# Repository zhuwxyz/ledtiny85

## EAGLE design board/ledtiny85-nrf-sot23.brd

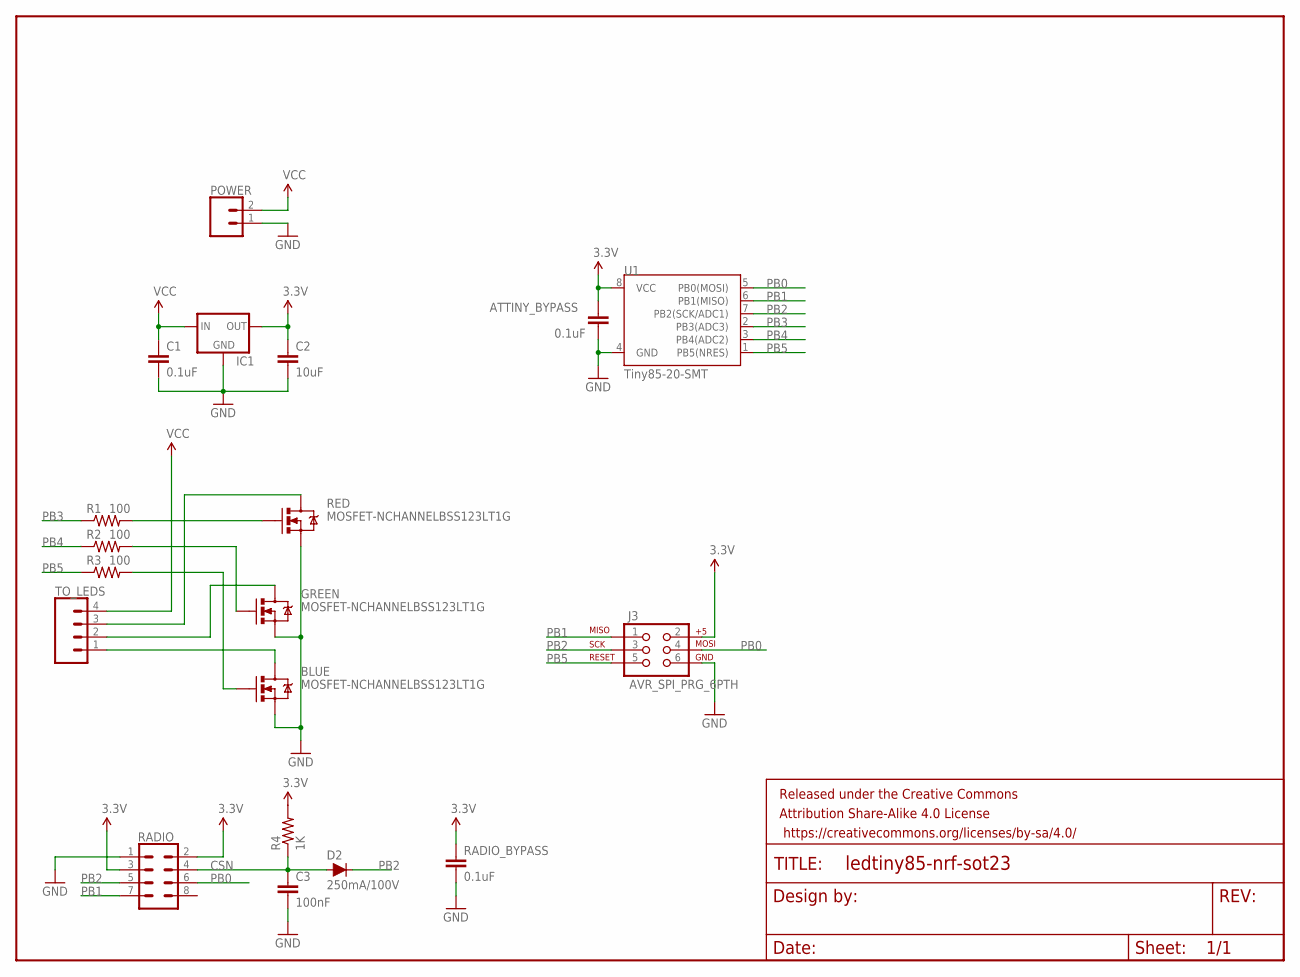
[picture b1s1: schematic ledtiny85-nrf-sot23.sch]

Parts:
ATTINY_BYPASS: 0.1uF; 0805
BLUE: MOSFET-NCHANNELBSS123LT1G; SOT23-3
C1: 0.1uF; 0805
C2: 10uF; 0805
C3: 100nF; 0805
D2: 250mA/100V; SOD-323
FRAME1: FRAME-LETTER; CREATIVE_COMMONS
GREEN: MOSFET-NCHANNELBSS123LT1G; SOT23-3
IC1: XC63FPM; SOT23
J3: AVR_SPI_PRG_6PTH; 2X3
POWER: CONN_02; 1X02
R1, R2, R3: 100; 0805
R4: 1K; 0805
RADIO: CONN_04X2; 2X4
RADIO_BYPASS: 0.1uF; 0805
RED: MOSFET-NCHANNELBSS123LT1G; SOT23-3
TO_LEDS: CONN_04; 1X04
U1: Tiny85-20-SMT; SO08-EIAJ

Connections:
3.3V: ATTINY_BYPASS.1, C2.1, IC1.2 (OUT), J3.2, R4.2, RADIO.2, RADIO.3, RADIO_BYPASS.1, U1.8 (VCC)
BLUE: BLUE.3 (D), TO_LEDS.1
CSN: C3.1, D2.A, R4.1, RADIO.4
GND: ATTINY_BYPASS.2, BLUE.2 (S), C1.2, C2.2, C3.2, GREEN.2 (S), IC1.1 (GND), J3.6, POWER.1, RADIO.1, RADIO_BYPASS.2, RED.2 (S), U1.4 (GND)
GREEN: GREEN.3 (D), TO_LEDS.2
unnamed: R1.2, RED.1 (G)
unnamed: GREEN.1 (G), R2.2
unnamed: BLUE.1 (G), R3.2
PB0: J3.4, RADIO.6, U1.5 (PB0(MOSI))
PB1: J3.1, RADIO.7, U1.6 (PB1(MISO))
PB2: D2.C, J3.3, RADIO.5, U1.7 (PB2(SCK/ADC1))
PB3: R1.1, U1.2 (PB3(ADC3))
PB4: R2.1, U1.3 (PB4(ADC2))
PB5: J3.5, R3.1, U1.1 (PB5(NRES))
RED: RED.3 (D), TO_LEDS.3
VCC: C1.1, IC1.3 (IN), POWER.2, TO_LEDS.4

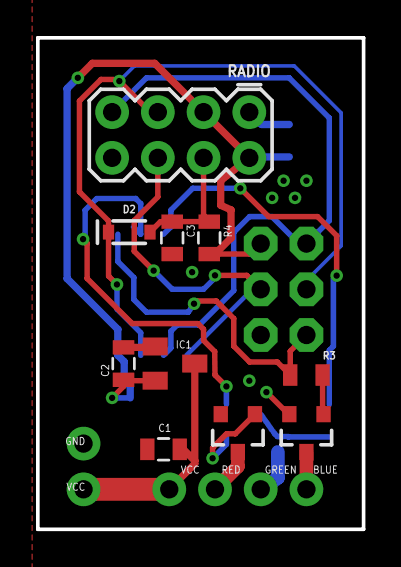
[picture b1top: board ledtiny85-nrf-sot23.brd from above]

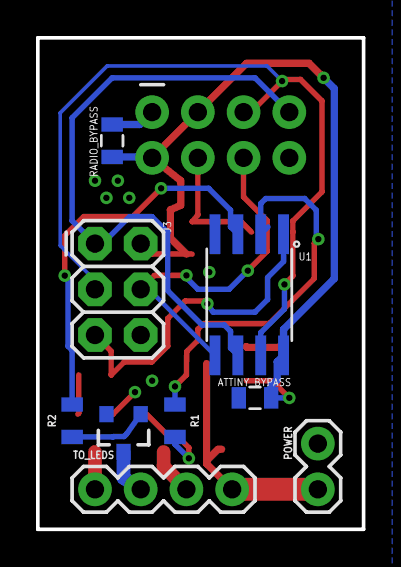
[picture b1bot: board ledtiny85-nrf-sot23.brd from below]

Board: 2 copper layers, 18.1 x 27.3 mm, 20 parts (9 on the bottom side), 16 nets.

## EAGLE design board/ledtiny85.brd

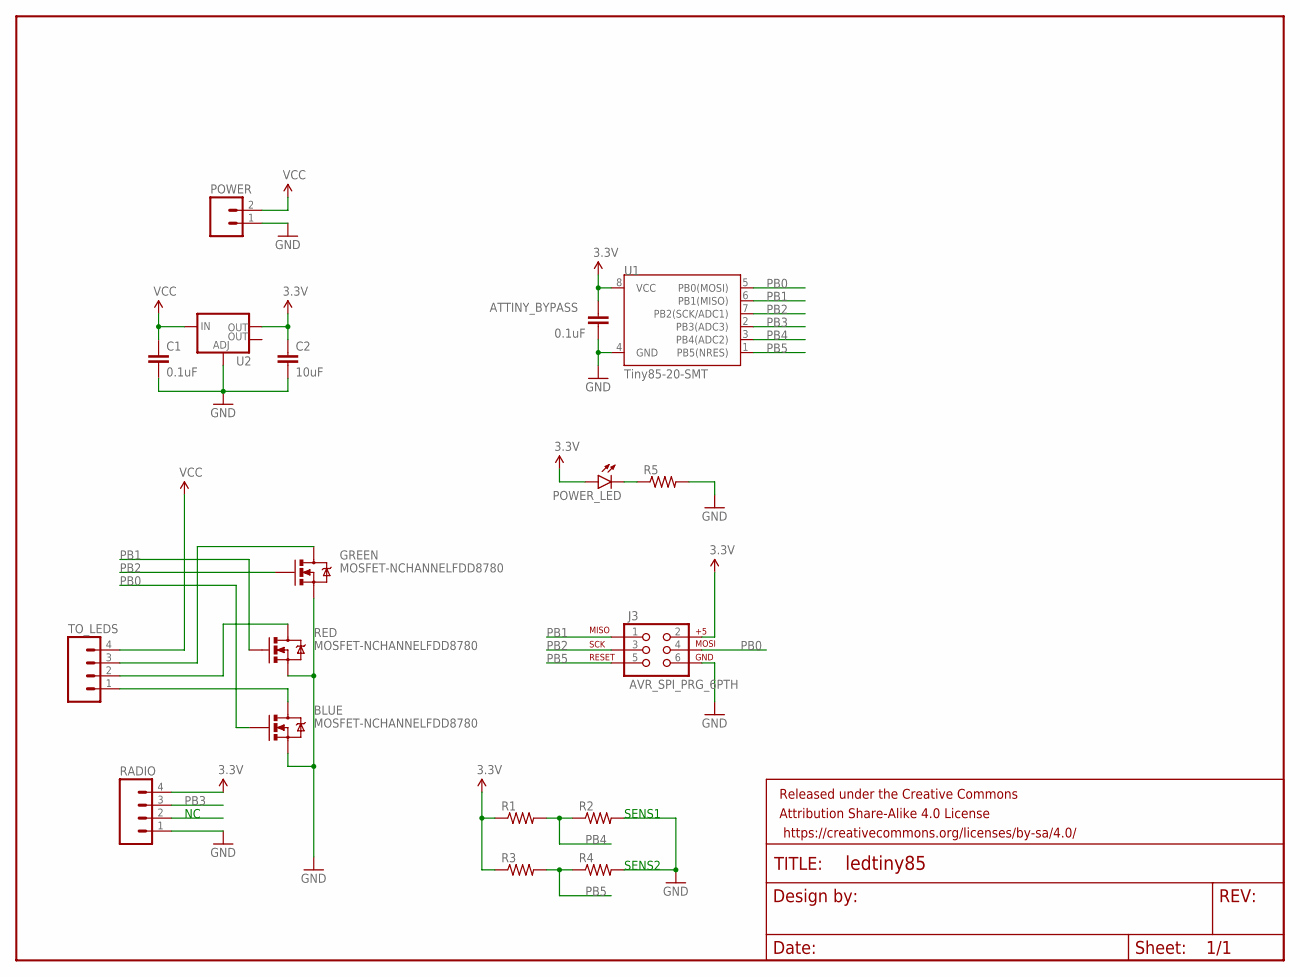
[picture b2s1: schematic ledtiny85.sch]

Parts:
ATTINY_BYPASS: 0.1uF; 1206
BLUE: MOSFET-NCHANNELFDD8780; DPAK
C1: 0.1uF; 1206
C2: 10uF; 1206
FRAME1: FRAME-LETTER; CREATIVE_COMMONS
GREEN: MOSFET-NCHANNELFDD8780; DPAK
J3: AVR_SPI_PRG_6PTH; 2X3
POWER: M02PTH3; 1X02_LONGPADS
POWER_LED: LED1206; LED-1206
R1, R2, R3, R4, R5: RESISTOR1206; 1206
RADIO: M04LONGPADS; 1X04_LONGPADS
RED: MOSFET-NCHANNELFDD8780; DPAK
TO_LEDS: M04LONGPADS; 1X04_LONGPADS
U1: Tiny85-20-SMT; SO08-EIAJ
U2: V_REG_LM1117SOT223; SOT223

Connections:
3.3V: ATTINY_BYPASS.1, C2.1, J3.2, POWER_LED.A, R1.1, R3.1, RADIO.4, U1.8 (VCC), U2.2 (OUT)
BLUE: BLUE.4 (D), TO_LEDS.1
GND: ATTINY_BYPASS.2, BLUE.3 (S), C1.2, C2.2, GREEN.3 (S), J3.6, POWER.1, R2.2, R4.2, R5.2, RADIO.1, RED.3 (S), U1.4 (GND), U2.1 (ADJ)
GREEN: RED.4 (D), TO_LEDS.2
unnamed: POWER_LED.C, R5.1
PB0: BLUE.1 (G), J3.4, U1.5 (PB0(MOSI))
PB1: J3.1, RED.1 (G), U1.6 (PB1(MISO))
PB2: GREEN.1 (G), J3.3, U1.7 (PB2(SCK/ADC1))
PB3: RADIO.3, U1.2 (PB3(ADC3))
PB4: R1.2, R2.1, U1.3 (PB4(ADC2))
PB5: J3.5, R3.2, R4.1, U1.1 (PB5(NRES))
RED: GREEN.4 (D), TO_LEDS.3
VCC: C1.1, POWER.2, TO_LEDS.4, U2.3 (IN)

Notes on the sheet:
SENS1
SENS2

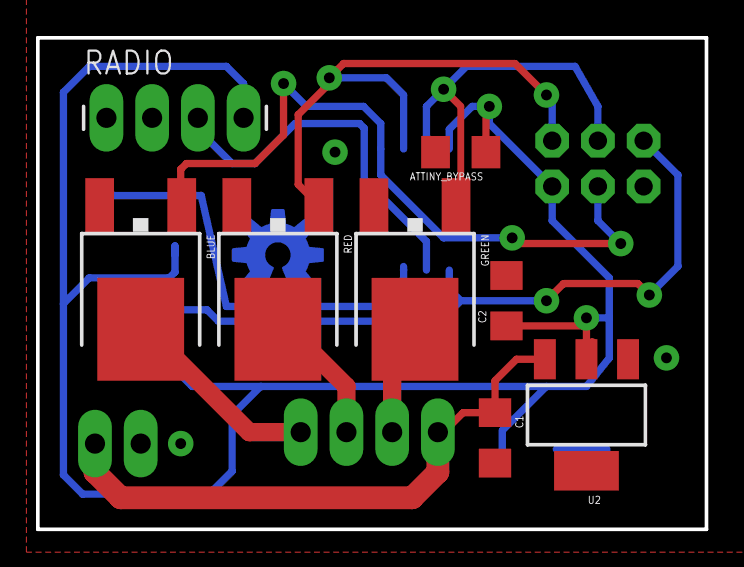
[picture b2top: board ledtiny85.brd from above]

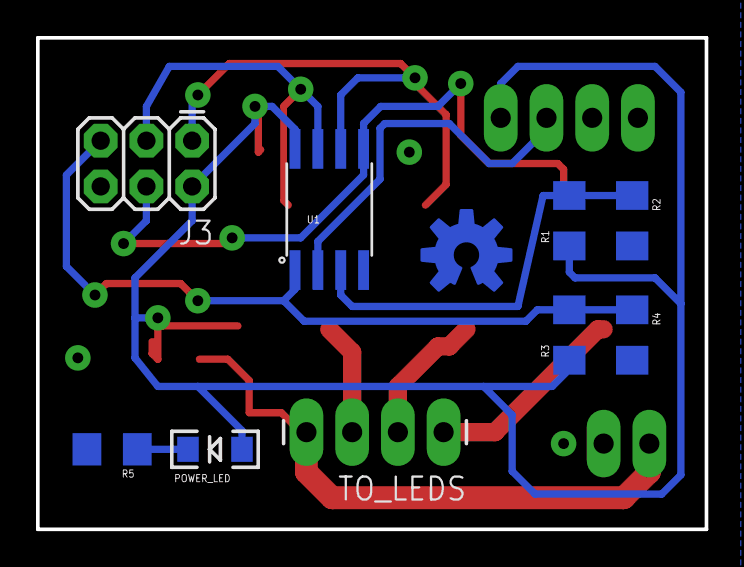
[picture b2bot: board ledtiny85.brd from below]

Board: 2 copper layers, 37.1 x 27.3 mm, 20 parts (11 on the bottom side), 13 nets.

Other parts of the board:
U$2: OSHW-LOGO-M_COPPER

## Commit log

2017-05-01 Add Eagle board files
2017-05-01 Add macOS to gitignore
2017-05-01 Add OSHW logo to board
2017-05-01 Make vias bigger
2017-05-05 Fix broken ground pour
2017-10-14 Add OSH Park design

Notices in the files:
parts and their libraries:
SparkFun-DiscreteSemi: Licensing: Creative Commons ShareAlike 4.0 International - https://creativecommons.org/licenses/by-sa/4.0
SparkFun-Aesthetics: Released under the Creative Commons Attribution Share-Alike 4.0 License
SparkFun-Aesthetics: https://creativecommons.org/licenses/by-sa/4.0
